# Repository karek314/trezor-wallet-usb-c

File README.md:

# Trezor Wallet USB-C
USB-C version of trezor hardware wallet designed to a bigger case

This is hardware project of forked <a href="https://github.com/trezor/trezor-hw">trezor-hw repository</a> redesigned to work with USB-C and a little bigger case.

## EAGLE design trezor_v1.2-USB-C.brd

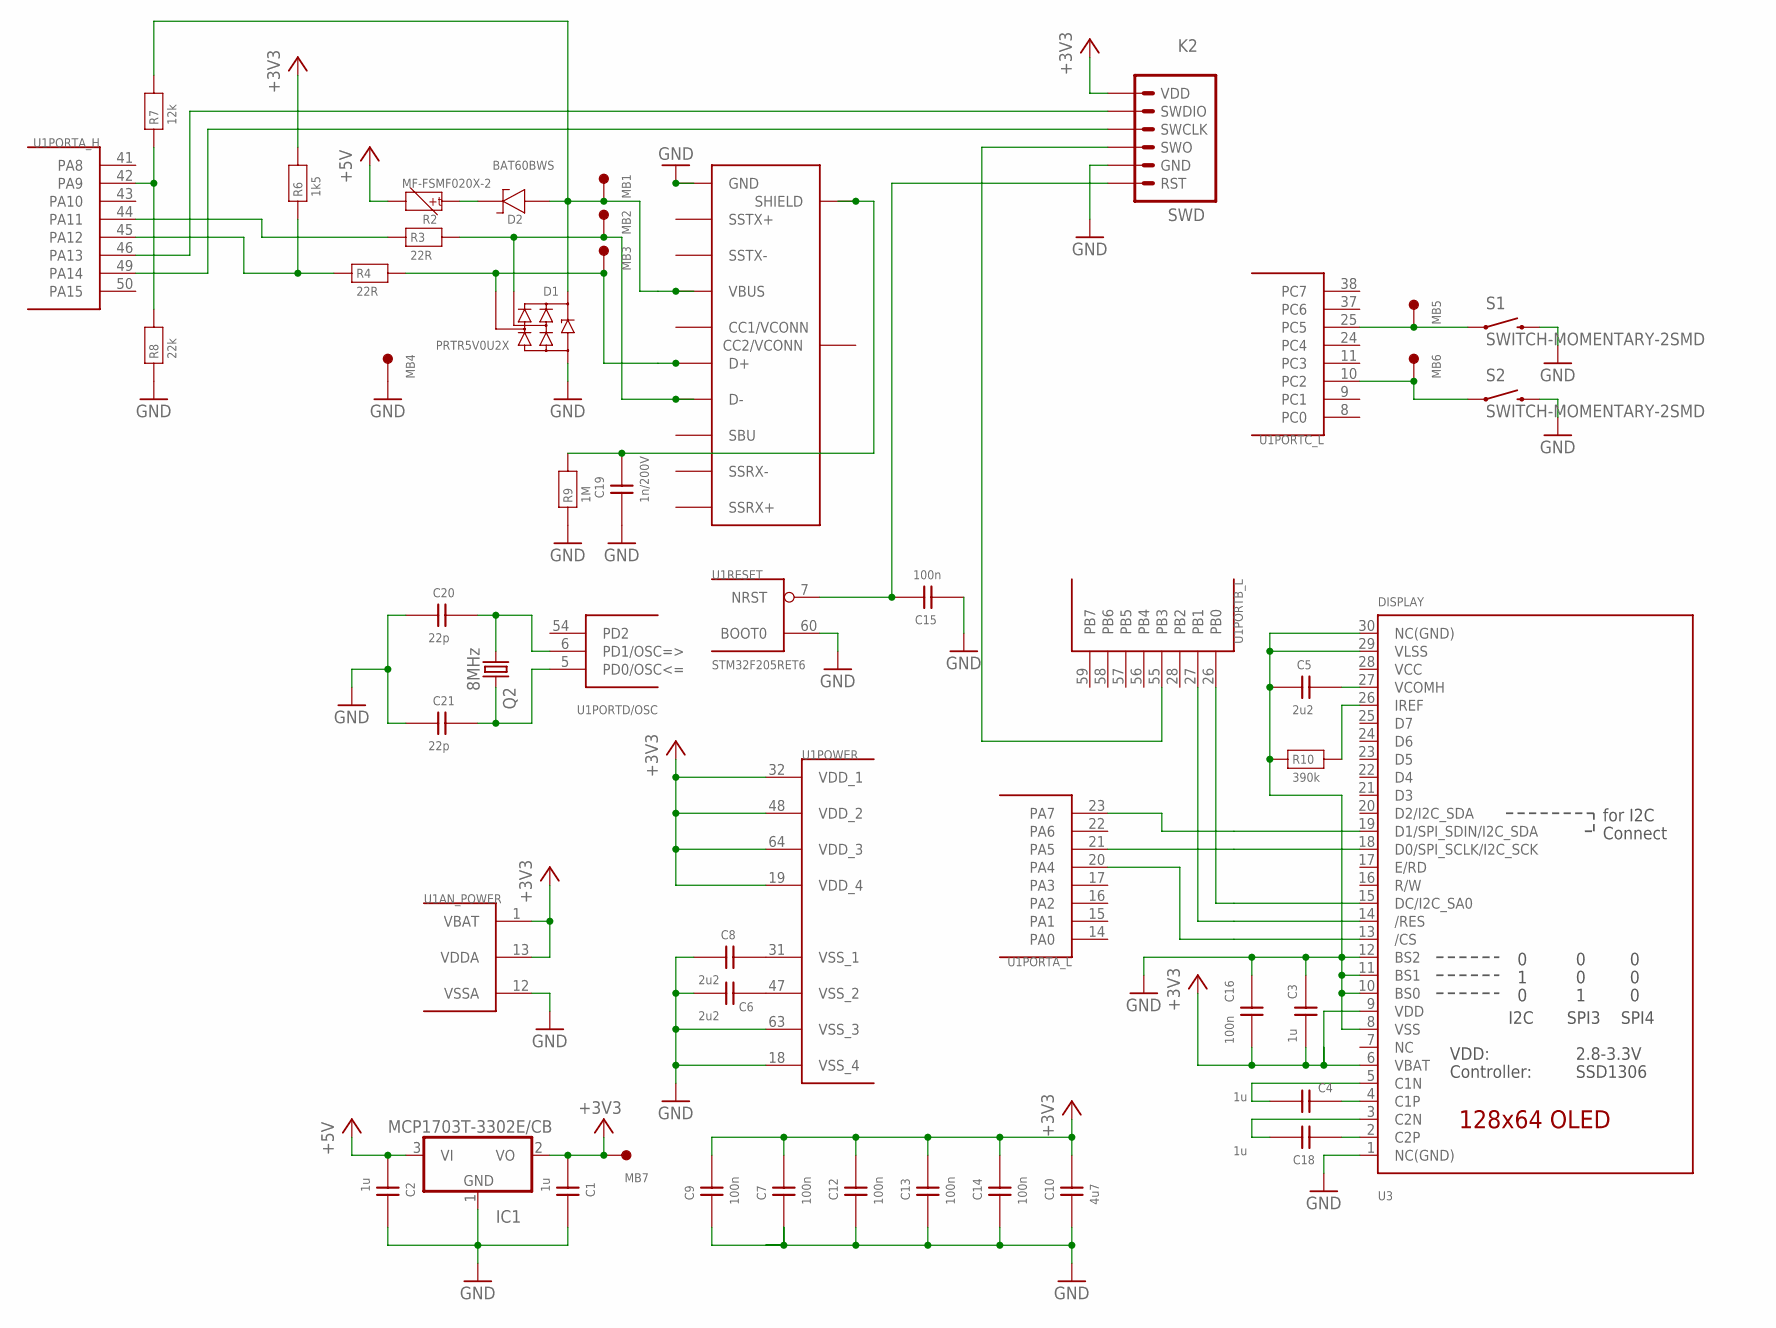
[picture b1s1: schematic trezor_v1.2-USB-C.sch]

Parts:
C1, C2, C3, C4, C18: 1u; 0402
C5: 2u2; 0603
C6, C8: 2u2; 0402
C7, C9, C12, C13, C14, C15, C16: 100n; 0402
C10: 4u7; 0603
C19: 1n/200V; 0603
C20, C21: 22p; 0402
D1: PRTR5V0U2X; SOT143B
D2: BAT60BWS; SOD323
IC1: MCP1703T-3302E/CB; SOT23
K2: SWD
MB1, MB2, MB3, MB4, MB5, MB6, MB7: MB_1.50; MB1.5
Q2: 8MHz; CTS406
R2: MF-FSMF020X-2; 0603
R3, R4: 22R; 0402
R6: 1k5; 0402
R7: 12k; 0402
R8: 22k; 0402
R9: 1M; 0603
R10: 390k; 0402
S1, S2: SWITCH-MOMENTARY-2SMD; TACTILE_SWITCH_SMD
U1: STM32F205RET6; TQFP64
U3: DISPLAY; UG-2864HSWEG01_0.96IN_WRAPAROUND
U$1: USB-TYPE-CHYBRID; USB-TYPE-C-HYBRID

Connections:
+3V3: C1.P$1 (1), C3.P$1 (1), C7.P$2 (2), C9.P$2 (2), C10.2, C12.P$2 (2), C13.P$2 (2), C14.P$2 (2), C16.P$1 (1), IC1.2 (VO), K2.6 (VDD), MB7.1, R6.P$2 (2), U1.1 (VBAT), U1.13 (VDDA), U1.19 (VDD_4), U1.32 (VDD_1), U1.48 (VDD_2), U1.64 (VDD_3), U3.6 (VBAT), U3.9 (VDD)
+5V: C2.P$1 (1), IC1.3 (VI), R2.2
GND: C1.P$2 (2), C2.P$2 (2), C3.P$2 (2), C5.1, C6.P$1 (1), C7.P$1 (1), C8.P$1 (1), C9.P$1 (1), C10.1, C12.P$1 (1), C13.P$1 (1), C14.P$1 (1), C15.P$1 (1), C16.P$2 (2), C19.1, C20.P$1 (1), C21.P$1 (1), D1.1 (GND), IC1.1 (GND), K2.2 (GND), MB4.1, R8.P$1 (1), R9.1, R10.P$1 (1), S1.3 (2), S1.4 (2), S2.3 (2), S2.4 (2), U1.12 (VSSA), U1.18 (VSS_4), U1.60 (BOOT0), U1.63 (VSS_3), U3.1 (NC(GND)), U3.8 (VSS), U3.10 (BS0), U3.11 (BS1), U3.12 (BS2), U3.29 (VLSS), U3.30 (NC(GND)), U$1.1 (GND), U$1.12 (GND), U$1.B1 (GND), U$1.B12 (GND)
unnamed: U1.23 (PA7), U3.19 (D1/SPI_SDIN/I2C_SDA)
unnamed: C15.P$2 (2), K2.1 (RST), U1.7 (NRST)
unnamed: U1.26 (PB0), U3.15 (DC/I2C_SA0)
unnamed: C8.P$2 (2), U1.31 (VSS_1)
unnamed: U1.21 (PA5), U3.18 (D0/SPI_SCLK/I2C_SCK)
unnamed: C5.2, U3.27 (VCOMH)
unnamed: U1.27 (PB1), U3.14 (/RES)
unnamed: C6.P$2 (2), U1.47 (VSS_2)
unnamed: R10.P$2 (2), U3.26 (IREF)
unnamed: C18.P$1 (1), U3.2 (C2P)
unnamed: C4.P$1 (1), U3.4 (C1P)
unnamed: C18.P$2 (2), U3.3 (C2N)
unnamed: C4.P$2 (2), U3.5 (C1N)
unnamed: K2.3 (SWO), U1.55 (PB3)
unnamed: K2.5 (SWDIO), U1.46 (PA13)
unnamed: U1.20 (PA4), U3.13 (/CS)
unnamed: K2.4 (SWCLK), U1.49 (PA14)
unnamed: R3.P$1 (1), U1.44 (PA11)
unnamed: MB5.1, S1.1, S1.2 (1), U1.25 (PC5)
unnamed: MB6.1, S2.1, S2.2 (1), U1.10 (PC2)
unnamed: D2.K (2), R2.1
unnamed: D1.2 (I/O1), MB2.1, R3.P$2 (2), U$1.7 (D-), U$1.B7 (D-)
unnamed: D1.3 (I/O2), MB3.1, R4.P$2 (2), U$1.6 (D+), U$1.B6 (D+)
unnamed: C19.2, R9.2, U$1.P$1 (SHIELD), U$1.P$2 (SHIELD), U$1.P$3 (SHIELD), U$1.P$4 (SHIELD), U$1.P$7 (SHIELD), U$1.P$8 (SHIELD), U$1.P$9 (SHIELD), U$1.P$10 (SHIELD), U$1.P$11 (SHIELD), U$1.P$12 (SHIELD), U$1.P$13 (SHIELD), U$1.P$14 (SHIELD), U$1.P$15 (SHIELD), U$1.P$16 (SHIELD), U$1.P$17 (SHIELD), U$1.P$18 (SHIELD), U$1.P$19 (SHIELD), U$1.P$20 (SHIELD), U$1.P$21 (SHIELD), U$1.P$22 (SHIELD), U$1.P$23 (SHIELD), U$1.P$24 (SHIELD), U$1.P$25 (SHIELD), U$1.P$26 (SHIELD), U$1.P$27 (SHIELD), U$1.P$28 (SHIELD), U$1.P$29 (SHIELD), U$1.P$30 (SHIELD), U$1.P$31 (SHIELD), U$1.P$32 (SHIELD), U$1.P$33 (SHIELD), U$1.P$34 (SHIELD), U$1.P$35 (SHIELD)
unnamed: R7.P$1 (1), R8.P$2 (2), U1.42 (PA9)
USB_D_P: R4.P$1 (1), R6.P$1 (1), U1.45 (PA12)
VBUS: D1.4 (VCC), D2.A (1), MB1.1, R7.P$2 (2), U$1.4 (VBUS), U$1.9 (VBUS), U$1.B4 (VBUS), U$1.B9 (VBUS)
VCC: U3.28 (VCC)
XTAL1: C20.P$2 (2), Q2.1, U1.6 (PD1/OSC=>)
XTAL2: C21.P$2 (2), Q2.3 (2), U1.5 (PD0/OSC<=)

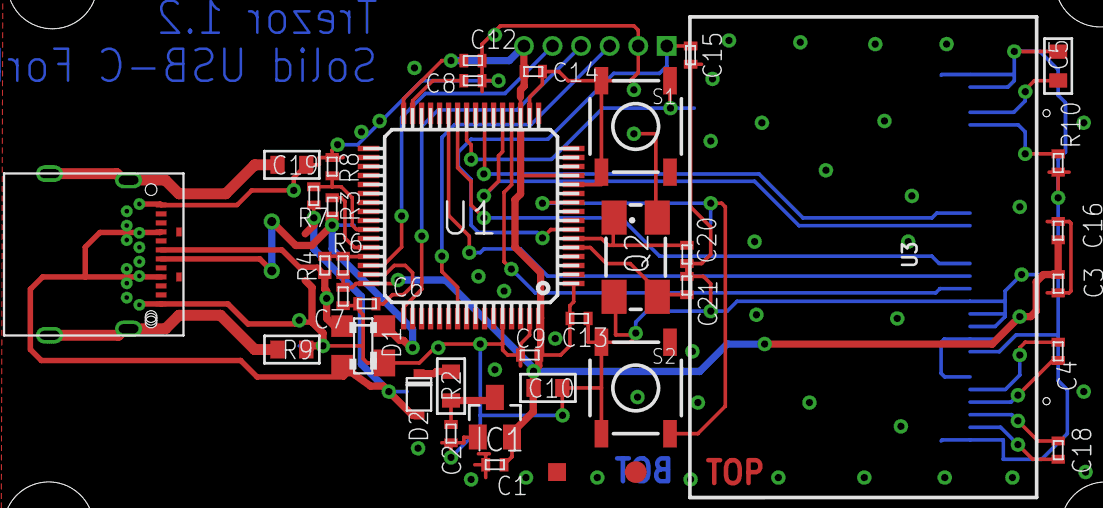
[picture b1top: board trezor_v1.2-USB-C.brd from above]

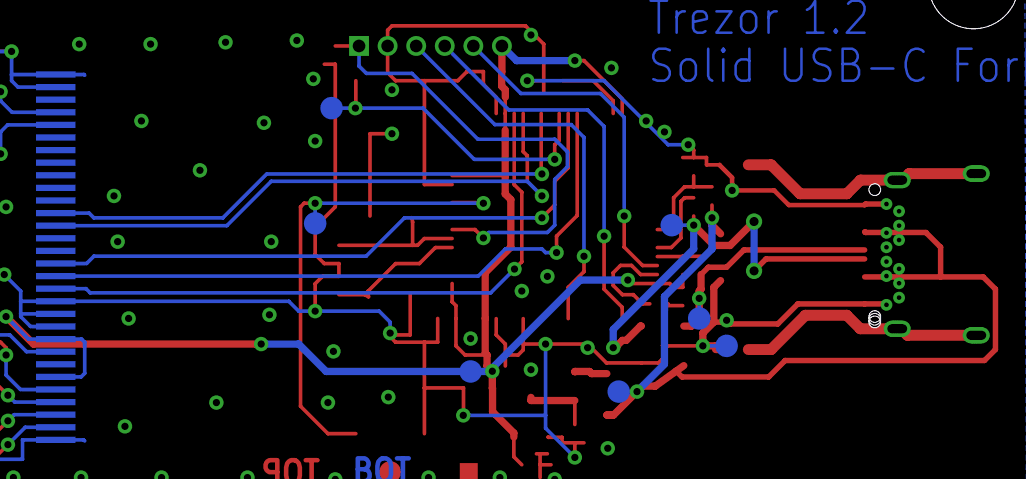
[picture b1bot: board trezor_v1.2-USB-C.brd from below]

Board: 2 copper layers, 46 parts (7 on the bottom side), 32 nets.

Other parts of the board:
U$3: BADMARK
U$4: CENTR

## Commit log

2018-04-29 Create LICENSE

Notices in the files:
parts and their libraries:
microbuilder: This work is placed in the public domain, and may be freely used for commercial and non-commercial work with the following conditions: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
SparkFun-Electromechanical: Licensing: CC v3.0 Share-Alike You are welcome to use this library for commercial purposes.
